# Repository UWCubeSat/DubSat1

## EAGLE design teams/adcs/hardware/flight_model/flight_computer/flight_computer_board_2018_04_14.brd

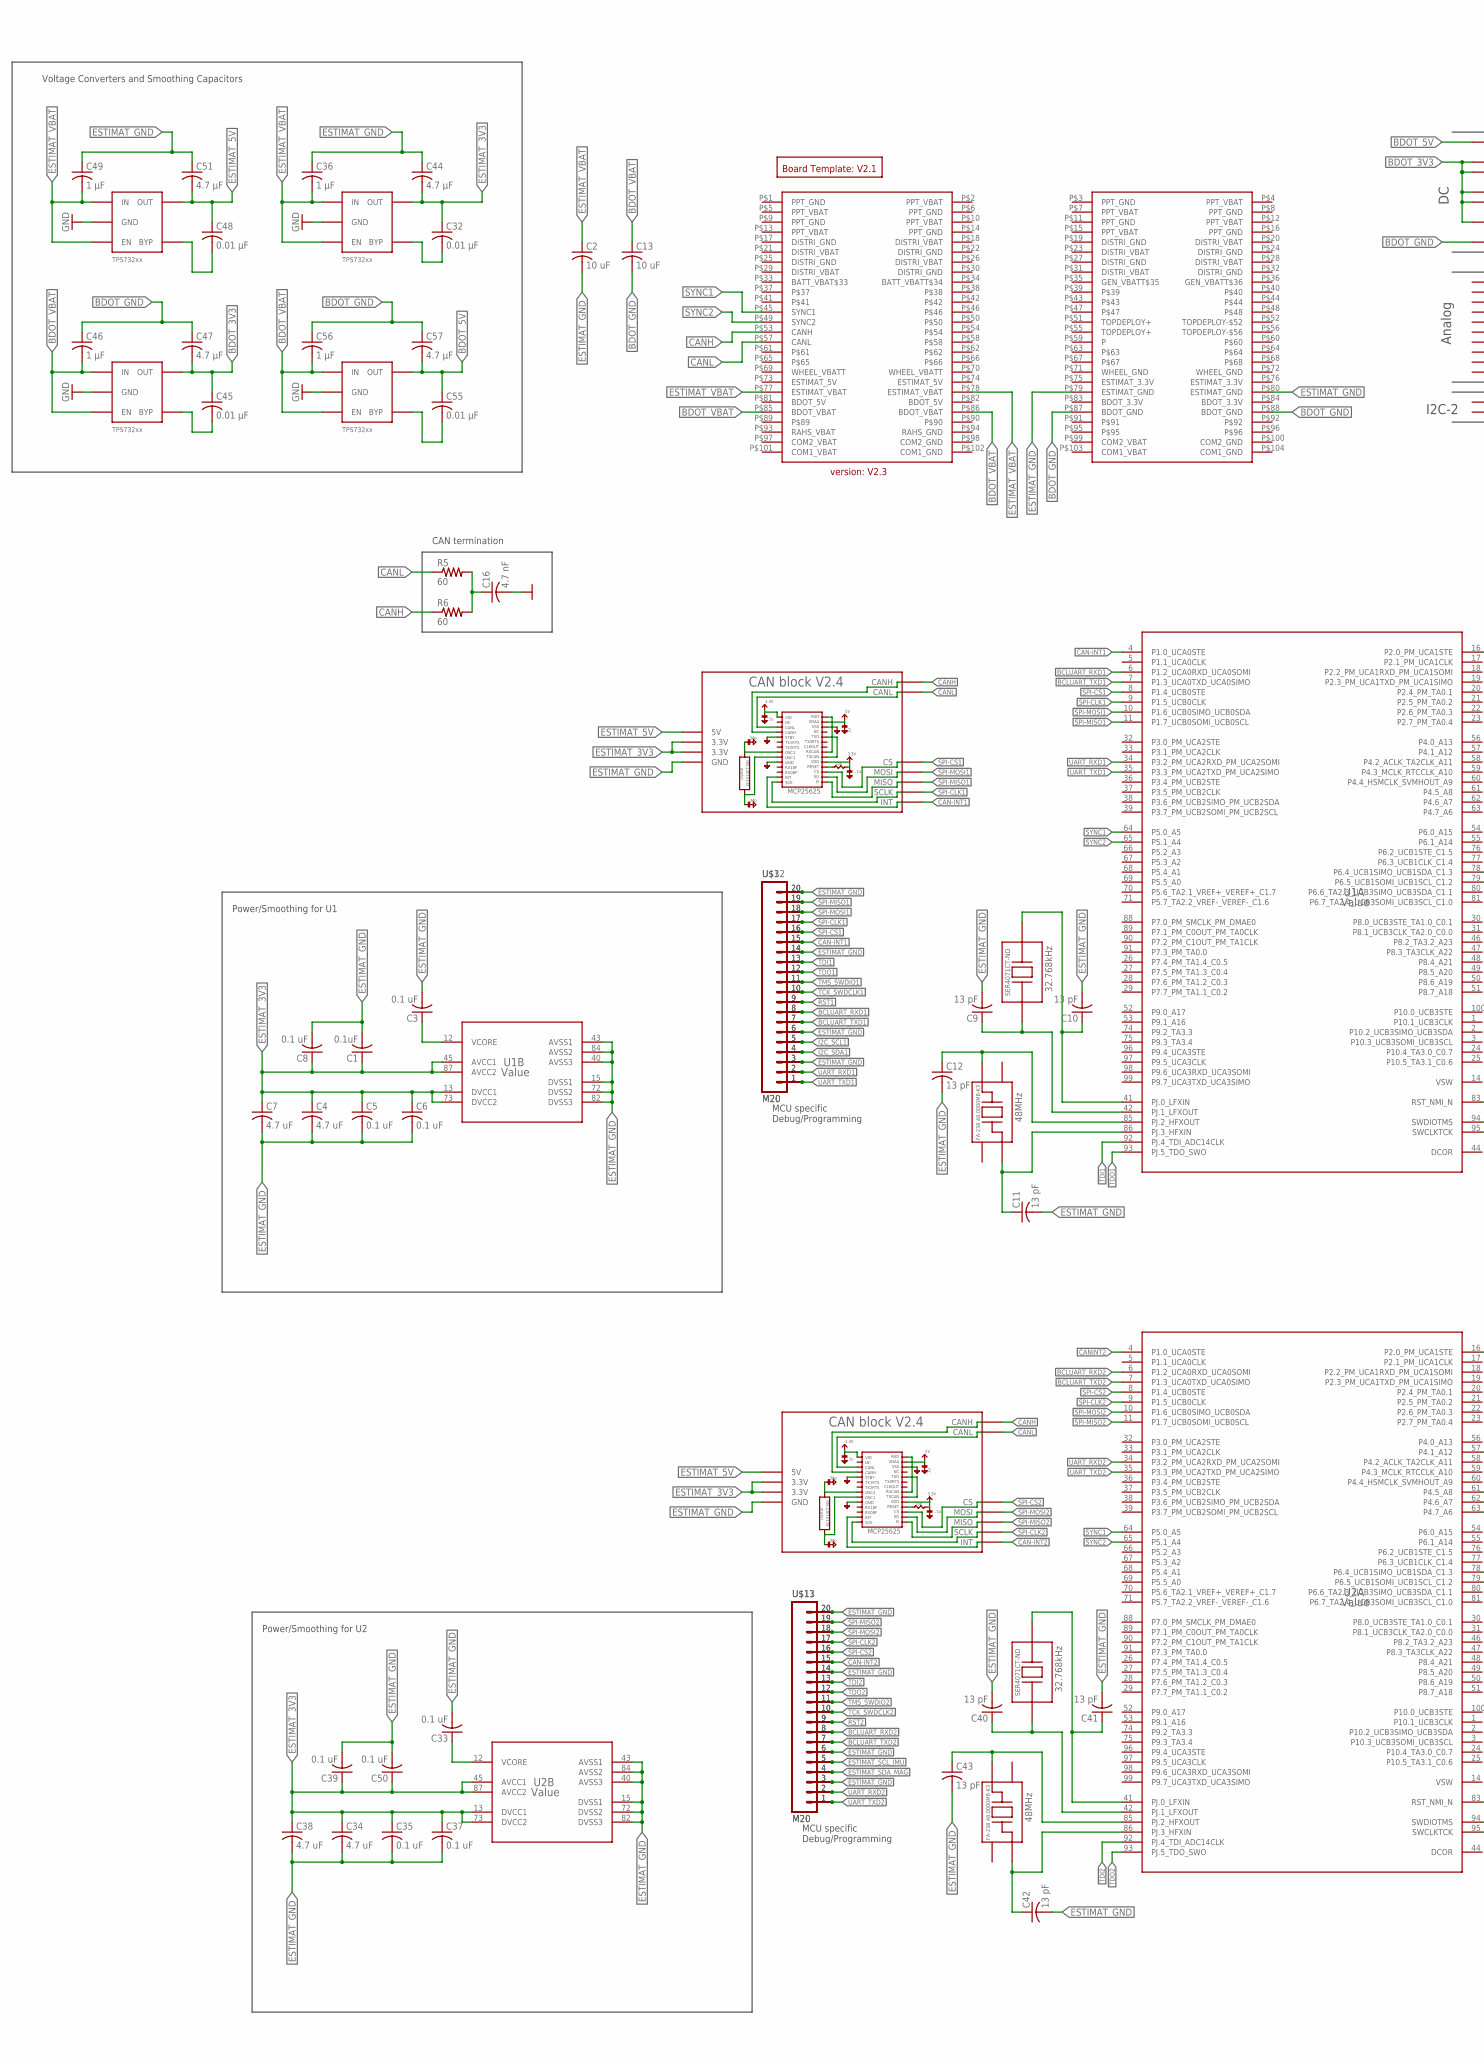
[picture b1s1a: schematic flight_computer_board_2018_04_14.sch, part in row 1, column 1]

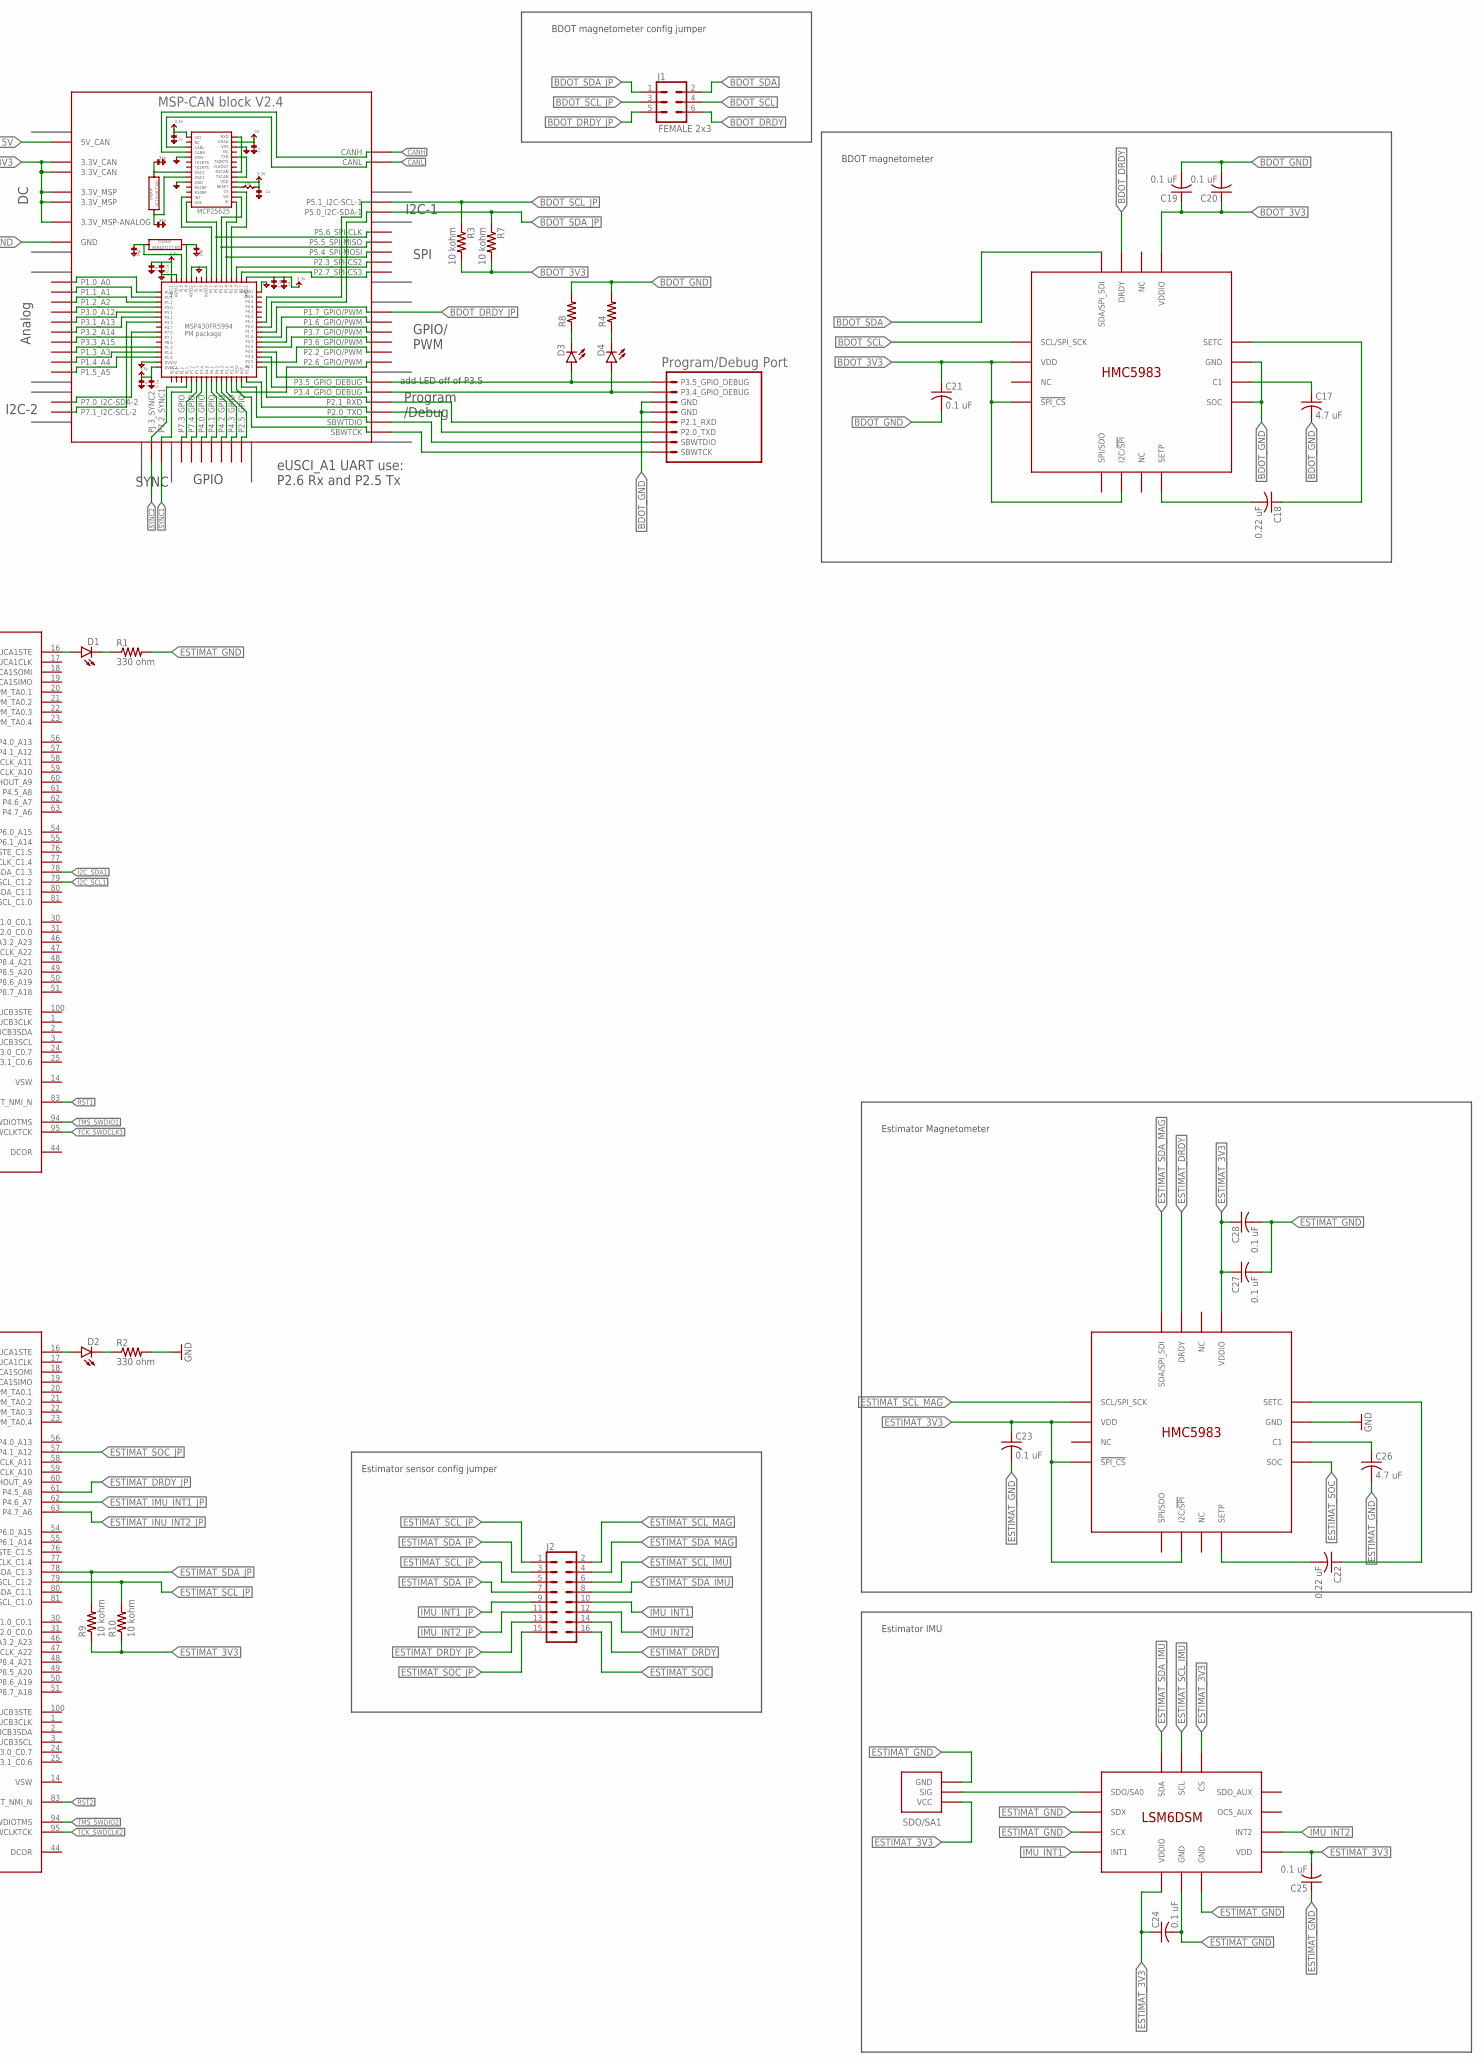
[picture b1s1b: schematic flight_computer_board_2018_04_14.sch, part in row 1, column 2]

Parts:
C1: 0.1uF; C0805
C2, C13: 10 uF; C0805
C3, C5, C6, C8, C19, C20, C21, C23, C24, C25, C27, C28, C33, C35, C37, C39, C50: 0.1 uF; C0805
C4, C7, C17, C26, C34, C38: 4.7 uF; C0805
C9, C10, C11, C12, C40, C41, C42, C43: 13 pF; C0805
C16: 4.7 nF; C0805
C18, C22: 0.22 uF; C0805
C32, C45, C48, C55: 0.01 μF; C0805
C36, C46, C49, C56: 1 μF; C0805
C44, C47, C51, C57: 4.7 μF; C0805
D1, D2, D3, D4: LED; LED-1206
J1: FEMALE 2x3; 2X3
J2: CONN_08X2; 2X8
R1, R2: 330 ohm; 0805
R3, R7, R9, R10: 10 kohm; 0805
R4, R8: RESISTOR0805; 0805
R5, R6: 60; 0805
SDO/SA1: 0_OHM_JUMPER
U1, U2: Value; PZ0100A_N
U4, U5, U6, U8: TPS732XX; SOT-23-5
U$1, U$4: EPSON_CRYSTAL_FC-135R; FC-135R
U$2, U$9: EPSON_CRYSTAL_FA-238; FA-238
U$3, U$11, U$12, U$13: M20; 1X20
U$5: BOARD_TEMPLATE1; BOARD_TEMPLATE
U$6: PC104_CONNECTOR
U$7: MSP-CAN_BLOCK
U$8, U$10: CAN_BLOCK
U$14: PROGRAM/DEBUG_PORT; 1X08_CONNECTOR
U$15, U$18: HMC5983
U$17: LSM6DSM

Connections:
BCLUART_RXD1: U1.6 (P1.2_UCA0RXD_UCA0SOMI), U$3.8, U$12.8
BCLUART_RXD2: U2.6 (P1.2_UCA0RXD_UCA0SOMI), U$11.8, U$13.8
BCLUART_TXD1: U1.7 (P1.3_UCA0TXD_UCA0SIMO), U$3.7, U$12.7
BCLUART_TXD2: U2.7 (P1.3_UCA0TXD_UCA0SIMO), U$11.7, U$13.7
BDOT_3V3: C19.1, C20.1, C21.1, C45.1, C47.2, R3.2, R7.2, U5.P$5 (OUT), U$7.3.3V@CAN1 (3.3V_CAN), U$7.3.3V@CAN2 (3.3V_CAN), U$7.3.3V@MSP1 (3.3V_MSP), U$7.3.3V@MSP2 (3.3V_MSP), U$7.3.3V_ANALOG@MSP2 (3.3V_MSP-ANALOG), U$15.!SPI_CS, U$15.I2C/!SPI, U$15.VDD, U$15.VDDIO
BDOT_5V: C55.1, C57.2, U8.P$5 (OUT), U$7.5V (5V_CAN)
BDOT_DRDY: J1.6, U$15.DRDY
BDOT_DRDY_JP: J1.5, U$7.P1.7_GPIO/PWM
BDOT_GND: C13.2, C17.2, C19.2, C20.2, C21.2, C46.1, C47.1, C56.1, C57.1, R4.2, R8.2, U5.P$2 (GND), U8.P$2 (GND), U$6.P$87 (BDOT_GND), U$6.P$88 (BDOT_GND), U$7.GND@1 (GND), U$7.GND@2 (GND), U$7.GND@3 (GND), U$7.GND@4 (GND), U$7.GND@5 (GND), U$7.GND@7 (GND), U$7.GND@8 (GND), U$7.GND@9 (GND), U$7.GND@10 (GND), U$7.GND@11 (GND), U$7.GND@12 (GND), U$7.GND@13 (GND), U$7.GND@14 (GND), U$7.GND@15 (GND), U$7.GND@16 (GND), U$7.GND@17 (GND), U$7.GND@26 (GND), U$14.5 (GND), U$14.6 (GND), U$15.GND, U$15.SOC
BDOT_LDO_3V3_BYP: C45.2, U5.P$4 (BYP)
BDOT_LDO_5V_BYP: C55.2, U8.P$4 (BYP)
BDOT_P3.4_GPIO_DEBUG: D4.A, U$7.P3.4_GPIO_DEBUG, U$14.7 (P3.4_GPIO_DEBUG)
BDOT_P3.5_GPIO_DEBUG: D3.A, U$7.P3.5_GPIO_DEBUG, U$14.8 (P3.5_GPIO_DEBUG)
BDOT_RXD: U$7.P2.1_RXD, U$14.4 (P2.1_RXD)
BDOT_SCL: J1.4, U$15.SCL/SPI_SCK
BDOT_SCL_JP: J1.3, R3.1, U$7.P5.1_I2C-SCL-1
BDOT_SDA: J1.2, U$15.SDA/SPI_SDI
BDOT_SDA_JP: J1.1, R7.1, U$7.P5.0_I2C-SDA-1
BDOT_TXD: U$7.P2.0_TXD, U$14.3 (P2.0_TXD)
BDOT_VBAT: C13.1, C46.2, C56.2, U5.P$1 (IN), U5.P$3 (EN), U8.P$1 (IN), U8.P$3 (EN), U$6.P$85 (BDOT_VBAT), U$6.P$86 (BDOT_VBAT)
CAN-INT1: U1.4 (P1.0_UCA0STE), U$3.15, U$8.INT, U$12.15
CAN-INT2: U$10.INT, U$11.15, U$13.15
CANH: R6.1, U$6.P$53 (CANH), U$7.CANH, U$8.CANH, U$10.CANH
CANINT2: U2.4 (P1.0_UCA0STE)
CANL: R5.1, U$6.P$57 (CANL), U$7.CANL, U$8.CANL, U$10.CANL
ESTIMAT_3V3: C1.1, C4.1, C5.1, C6.1, C7.1, C8.1, C23.1, C24.1, C25.2, C27.1, C28.1, C32.1, C34.1, C35.1, C37.1, C38.1, C39.1, C44.2, C50.1, R9.1, R10.1, SDO/SA1.P$3 (VCC), U1.13 (DVCC1), U1.45 (AVCC1), U1.73 (DVCC2), U1.87 (AVCC2), U2.13 (DVCC1), U2.45 (AVCC1), U2.73 (DVCC2), U2.87 (AVCC2), U4.P$5 (OUT), U$8.3.3V@CAN1 (3.3V), U$8.3.3V@CAN2 (3.3V), U$10.3.3V@CAN1 (3.3V), U$10.3.3V@CAN2 (3.3V), U$17.CS, U$17.VDD, U$17.VDDIO, U$18.!SPI_CS, U$18.I2C/!SPI, U$18.VDD, U$18.VDDIO
ESTIMAT_5V: C48.1, C51.2, U6.P$5 (OUT), U$8.5V, U$10.5V
ESTIMAT_DRDY: J2.14, U$18.DRDY
ESTIMAT_DRDY_JP: J2.13, U2.61 (P4.5_A8)
ESTIMAT_GND: C1.2, C2.2, C3.2, C4.2, C5.2, C6.2, C7.2, C8.2, C9.2, C10.2, C11.2, C12.2, C16.2, C23.2, C24.2, C25.1, C26.2, C27.2, C28.2, C33.2, C34.2, C35.2, C36.1, C37.2, C38.2, C39.2, C40.2, C41.2, C42.2, C43.2, C44.1, C49.1, C50.2, C51.1, R1.2, R2.2, SDO/SA1.P$1 (GND), U1.15 (DVSS1), U1.40 (AVSS3), U1.43 (AVSS1), U1.72 (DVSS2), U1.82 (DVSS3), U1.84 (AVSS2), U2.15 (DVSS1), U2.40 (AVSS3), U2.43 (AVSS1), U2.72 (DVSS2), U2.82 (DVSS3), U2.84 (AVSS2), U4.P$2 (GND), U6.P$2 (GND), U$3.3, U$3.6, U$3.14, U$3.20, U$6.P$79 (ESTIMAT_GND), U$6.P$80 (ESTIMAT_GND), U$8.GND@1 (GND), U$8.GND@2 (GND), U$8.GND@3 (GND), U$8.GND@4 (GND), U$8.GND@5 (GND), U$8.GND@11 (GND), U$8.GND@12 (GND), U$8.GND@13 (GND), U$10.GND@1 (GND), U$10.GND@2 (GND), U$10.GND@3 (GND), U$10.GND@4 (GND), U$10.GND@5 (GND), U$10.GND@11 (GND), U$10.GND@12 (GND), U$10.GND@13 (GND), U$11.3, U$11.6, U$11.14, U$11.20, U$12.3, U$12.6, U$12.14, U$12.20, U$13.3, U$13.6, U$13.14, U$13.20, U$17.GND@1 (GND), U$17.GND@2 (GND), U$17.SCX, U$17.SDX, U$18.GND
ESTIMAT_IMU_INT1_JP: U2.62 (P4.6_A7)
ESTIMAT_INU_INT2_JP: U2.63 (P4.7_A6)
ESTIMAT_LDO_3V3_BYP: C32.2, U4.P$4 (BYP)
ESTIMAT_LDO_5V_BYP: C48.2, U6.P$4 (BYP)
ESTIMAT_SCL_IMU: J2.6, U$11.5, U$13.5, U$17.SCL
ESTIMAT_SCL_JP: J2.1, J2.5, R10.2, U2.79 (P6.5_UCB1SOMI_UCB1SCL_C1.2)
ESTIMAT_SCL_MAG: J2.2, U$18.SCL/SPI_SCK
ESTIMAT_SDA_IMU: J2.8, U$17.SDA
ESTIMAT_SDA_JP: J2.3, J2.7, R9.2, U2.78 (P6.4_UCB1SIMO_UCB1SDA_C1.3)
ESTIMAT_SDA_MAG: J2.4, U$11.4, U$13.4, U$18.SDA/SPI_SDI
ESTIMAT_SOC: J2.16, U$18.SOC
ESTIMAT_SOC_JP: J2.15, U2.57 (P4.1_A12)
ESTIMAT_VBAT: C2.1, C36.2, C49.2, U4.P$1 (IN), U4.P$3 (EN), U6.P$1 (IN), U6.P$3 (EN), U$6.P$77 (ESTIMAT_VBAT), U$6.P$78 (ESTIMAT_VBAT)
I2C_SCL1: U1.79 (P6.5_UCB1SOMI_UCB1SCL_C1.2), U$3.5, U$12.5
I2C_SDA1: U1.78 (P6.4_UCB1SIMO_UCB1SDA_C1.3), U$3.4, U$12.4
IMU_INT1: J2.10, U$17.INT1
IMU_INT1_JP: J2.9
IMU_INT2: J2.12, U$17.INT2
IMU_INT2_JP: J2.11
unnamed: D2.A, U2.16 (P2.0_PM_UCA1STE)
unnamed: D2.C, R2.1
unnamed: D1.A, U1.16 (P2.0_PM_UCA1STE)
unnamed: D1.C, R1.1
unnamed: C3.1, U1.12 (VCORE)
unnamed: C10.1, U1.41 (PJ.0_LFXIN), U$1.P$2
unnamed: C9.1, U1.42 (PJ.1_LFXOUT), U$1.P$1
unnamed: C12.1, U1.85 (PJ.2_HFXOUT), U$2.P$3
unnamed: C11.1, U1.86 (PJ.3_HFXIN), U$2.P$1
unnamed: D4.C, R4.1
unnamed: C16.1, R5.2, R6.2
unnamed: D3.C, R8.1
unnamed: C17.1, U$15.C1
unnamed: C18.2, U$15.SETP
unnamed: C18.1, U$15.SETC
unnamed: SDO/SA1.P$2 (SIG), U$17.SDO/SA0
unnamed: C26.1, U$18.C1
unnamed: C22.2, U$18.SETP
unnamed: C22.1, U$18.SETC
unnamed: C40.1, U2.42 (PJ.1_LFXOUT), U$4.P$1
unnamed: C41.1, U2.41 (PJ.0_LFXIN), U$4.P$2
unnamed: C42.1, U2.86 (PJ.3_HFXIN), U$9.P$1
unnamed: C43.1, U2.85 (PJ.2_HFXOUT), U$9.P$3
RST1: U1.83 (RST_NMI_N), U$3.9, U$12.9
RST2: U2.83 (RST_NMI_N), U$11.9, U$13.9
SBWTCK: U$7.SBWTCK, U$14.SBWTCK
SBWTDIO: U$7.SBWTDIO, U$14.2 (SBWTDIO)
SPI-CLK1: U1.9 (P1.5_UCB0CLK), U$3.17, U$8.CLK (SCLK), U$12.17
SPI-CLK2: U2.9 (P1.5_UCB0CLK), U$10.CLK (SCLK), U$11.17, U$13.17
SPI-CS1: U1.8 (P1.4_UCB0STE), U$3.16, U$8.CS, U$12.16
SPI-CS2: U2.8 (P1.4_UCB0STE), U$10.CS, U$11.16, U$13.16
SPI-MISO1: U1.11 (P1.7_UCB0SOMI_UCB0SCL), U$3.19, U$8.MISO, U$12.19
SPI-MISO2: U2.11 (P1.7_UCB0SOMI_UCB0SCL), U$10.MISO, U$11.19, U$13.19
SPI-MOSI1: U1.10 (P1.6_UCB0SIMO_UCB0SDA), U$3.18, U$8.MOSI, U$12.18
SPI-MOSI2: U2.10 (P1.6_UCB0SIMO_UCB0SDA), U$10.MOSI, U$11.18, U$13.18
SYNC1: U1.64 (P5.0_A5), U2.64 (P5.0_A5), U$6.P$45 (SYNC1), U$7.P7.2_SYNC1
SYNC2: U1.65 (P5.1_A4), U2.65 (P5.1_A4), U$6.P$49 (SYNC2), U$7.PJ.3_SYNC2
TCK_SWDCLK1: U1.95 (SWCLKTCK), U$3.10, U$12.10
TCK_SWDCLK2: U2.95 (SWCLKTCK), U$11.10, U$13.10
TDI1: U1.92 (PJ.4_TDI_ADC14CLK), U$3.13, U$12.13
TDI2: U2.92 (PJ.4_TDI_ADC14CLK), U$11.13, U$13.13
TDO1: U1.93 (PJ.5_TDO_SWO), U$3.12, U$12.12
TDO2: U2.93 (PJ.5_TDO_SWO), U$11.12, U$13.12
TMS_SWDIO1: U1.94 (SWDIOTMS), U$3.11, U$12.11
TMS_SWDIO2: U2.94 (SWDIOTMS), U$11.11, U$13.11
UART_RXD1: U1.34 (P3.2_PM_UCA2RXD_PM_UCA2SOMI), U$3.2, U$12.2
UART_RXD2: U2.34 (P3.2_PM_UCA2RXD_PM_UCA2SOMI), U$11.2, U$13.2
UART_TXD1: U1.35 (P3.3_PM_UCA2TXD_PM_UCA2SIMO), U$3.1, U$12.1
UART_TXD2: U2.35 (P3.3_PM_UCA2TXD_PM_UCA2SIMO), U$11.1, U$13.1
VCORE: C33.1, U2.12 (VCORE)

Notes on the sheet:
MCU specific Debug/Programming
CAN termination
Voltage Converters and Smoothing Capacitors
Power/Smoothing for U2
Power/Smoothing for U1
Estimator IMU
Estimator Magnetometer
BDOT magnetometer
BDOT magnetometer config jumper
Estimator sensor config jumper

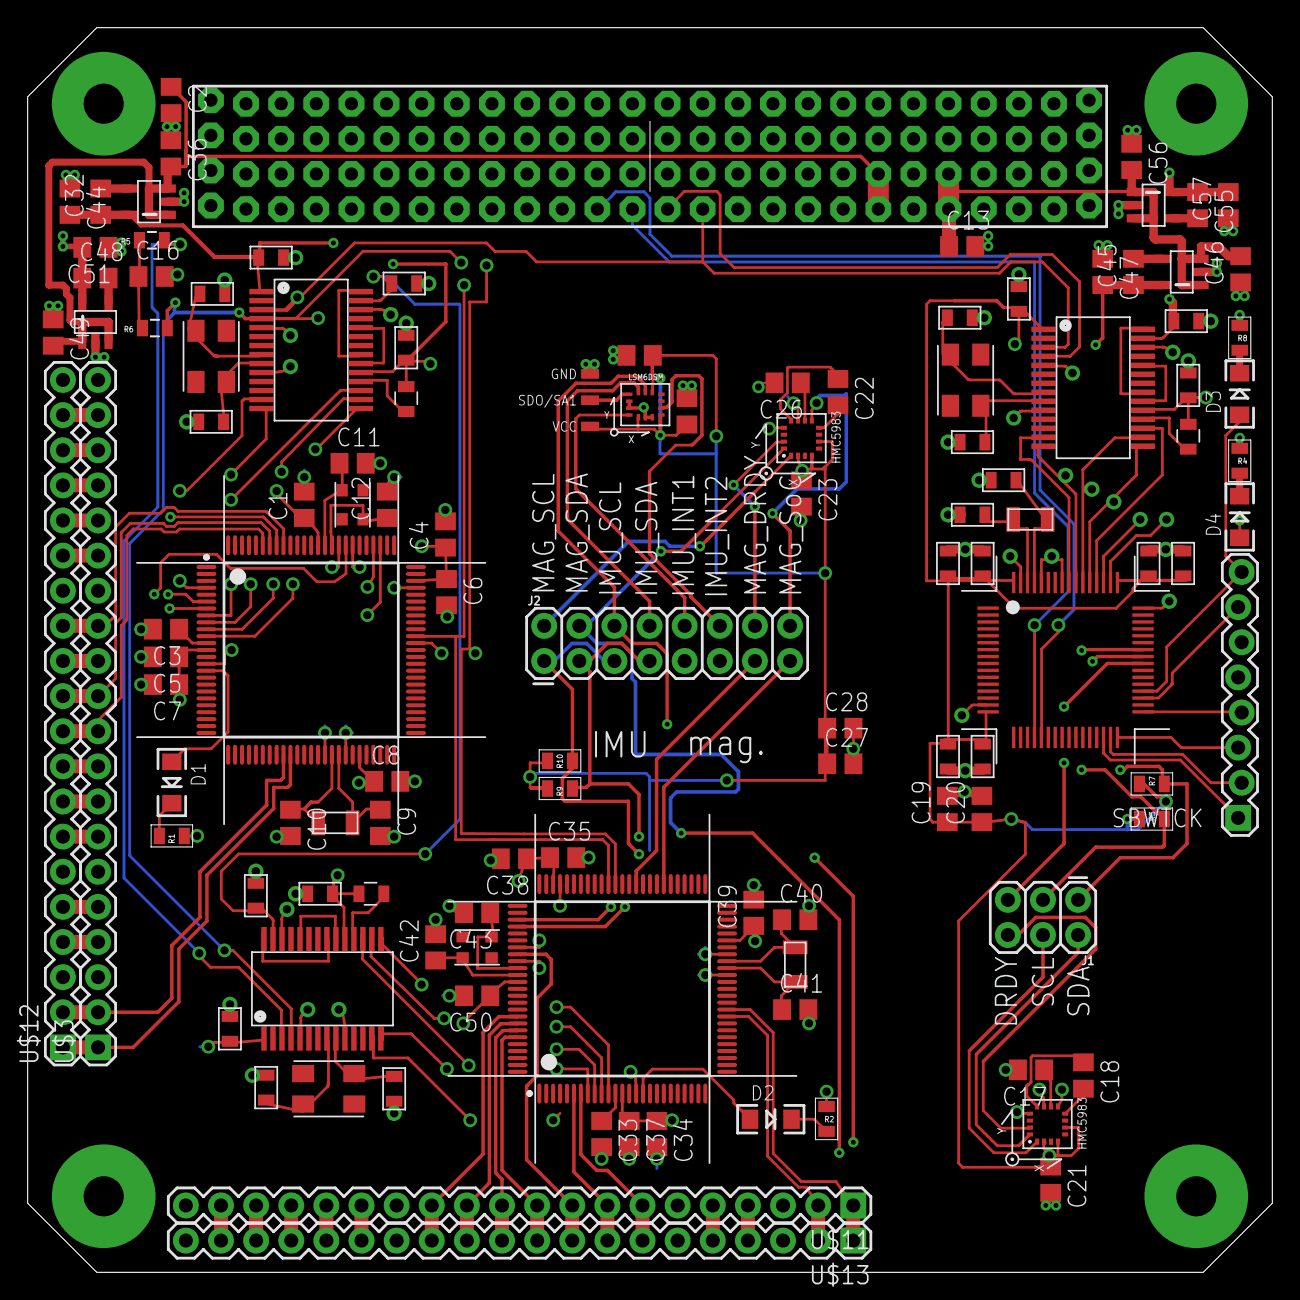
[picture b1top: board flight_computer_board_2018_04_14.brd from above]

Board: 4 copper layers, 90.0 x 90.0 mm, 89 parts (0 on the bottom side), 94 nets.

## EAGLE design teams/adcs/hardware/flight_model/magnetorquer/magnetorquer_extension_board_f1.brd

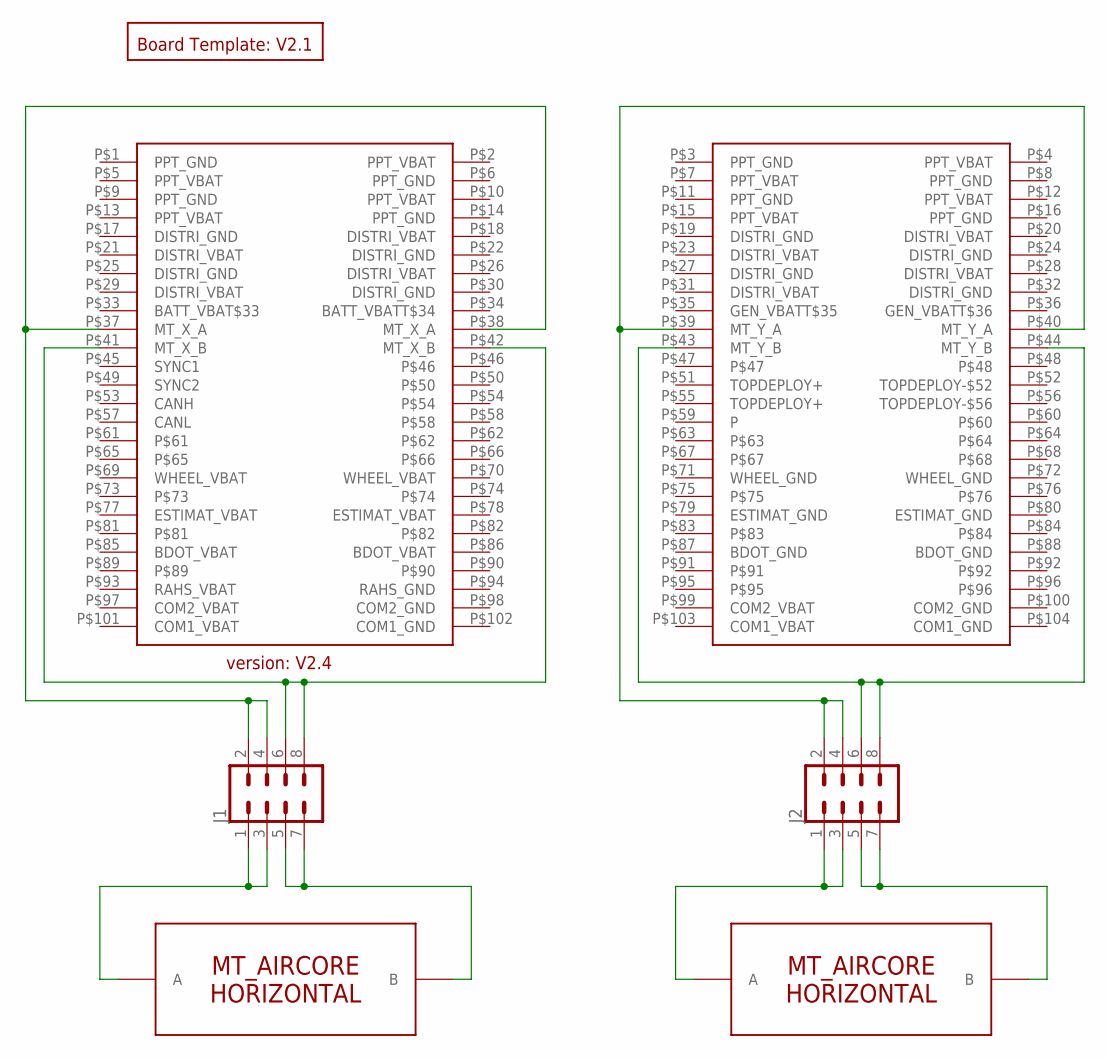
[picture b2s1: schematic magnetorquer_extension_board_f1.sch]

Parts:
J1, J2: CONN_04X2; 2X4
MT_X: MT_AIRCORE_HORIZONTAL
MT_Y: MT_AIRCORE_HORIZONTAL
U$1: PC104_CONNECTOR
U$2: BOARD_TEMPLATESERCURED; BOARD_TEMPLATE_SECURED

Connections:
MT_X_A: J1.1, J1.3, MT_X.A
MT_X_A_STACK: J1.2, J1.4, U$1.P$37 (MT_X_A), U$1.P$38 (MT_X_A)
MT_X_B: J1.5, J1.7, MT_X.B
MT_X_B_STACK: J1.6, J1.8, U$1.P$41 (MT_X_B), U$1.P$42 (MT_X_B)
MT_Y_A: J2.1, J2.3, MT_Y.A
MT_Y_A_STACK: J2.2, J2.4, U$1.P$39 (MT_Y_A), U$1.P$40 (MT_Y_A)
MT_Y_B: J2.5, J2.7, MT_Y.B
MT_Y_B_STACK: J2.6, J2.8, U$1.P$43 (MT_Y_B), U$1.P$44 (MT_Y_B)

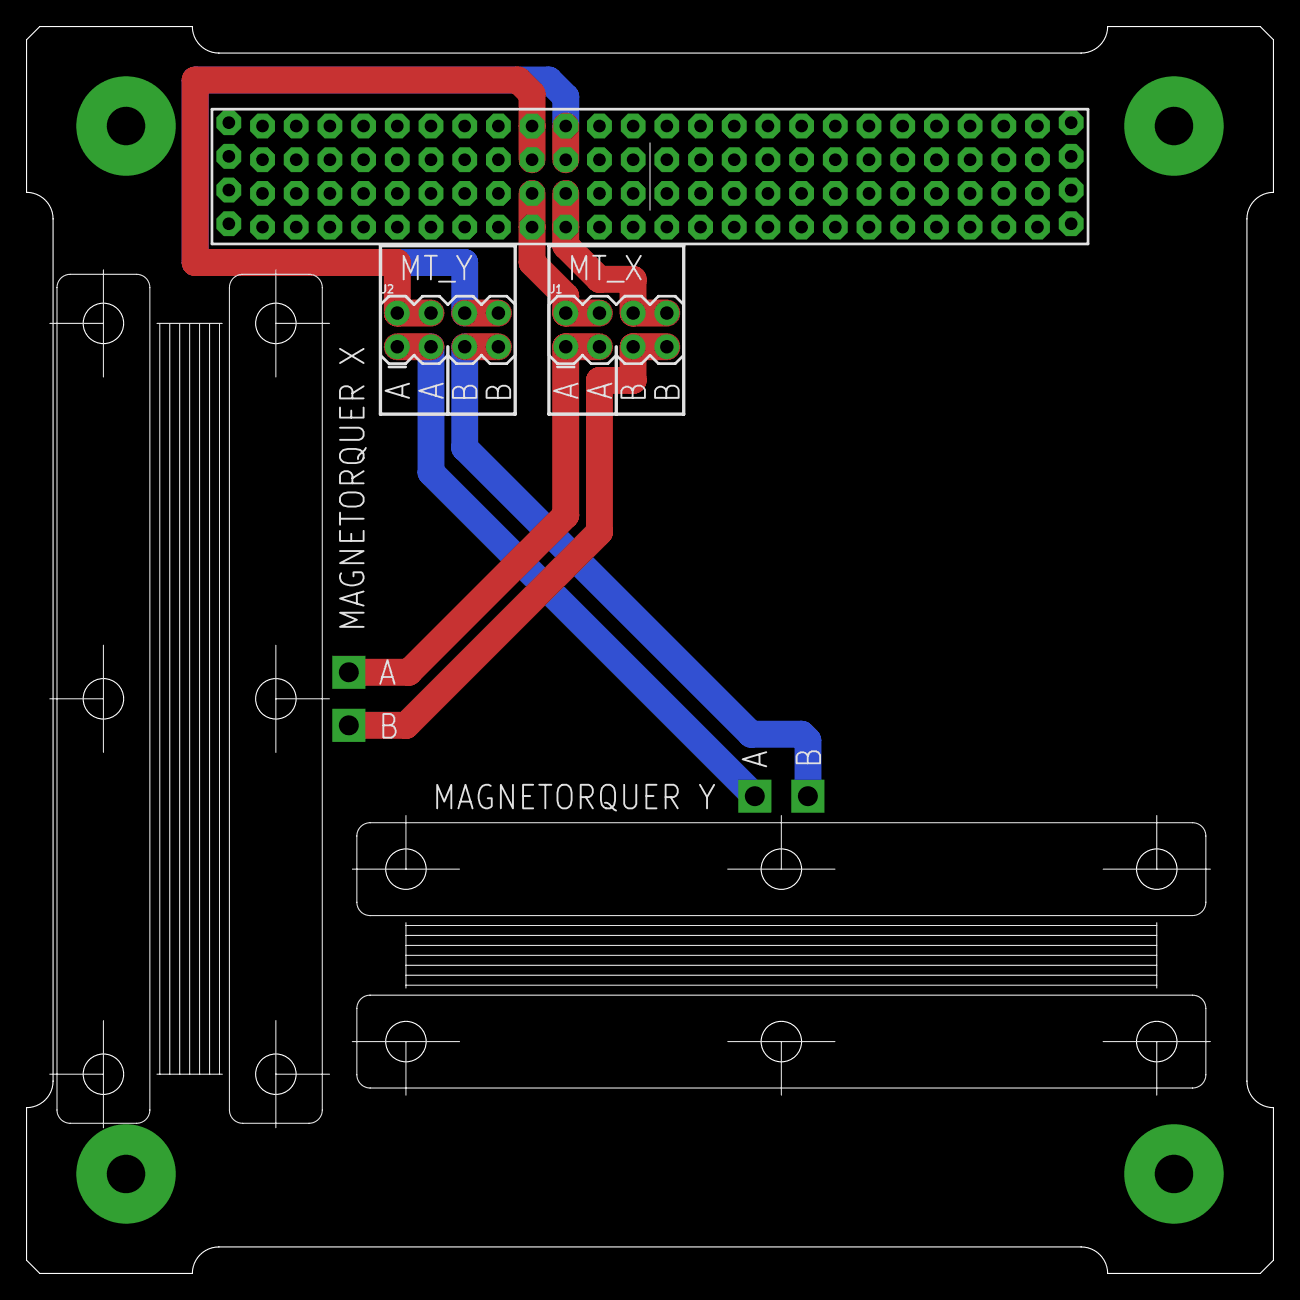
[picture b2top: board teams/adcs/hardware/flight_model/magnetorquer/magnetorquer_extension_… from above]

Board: 2 copper layers, 94.0 x 94.0 mm, 6 parts (0 on the bottom side), 8 nets.

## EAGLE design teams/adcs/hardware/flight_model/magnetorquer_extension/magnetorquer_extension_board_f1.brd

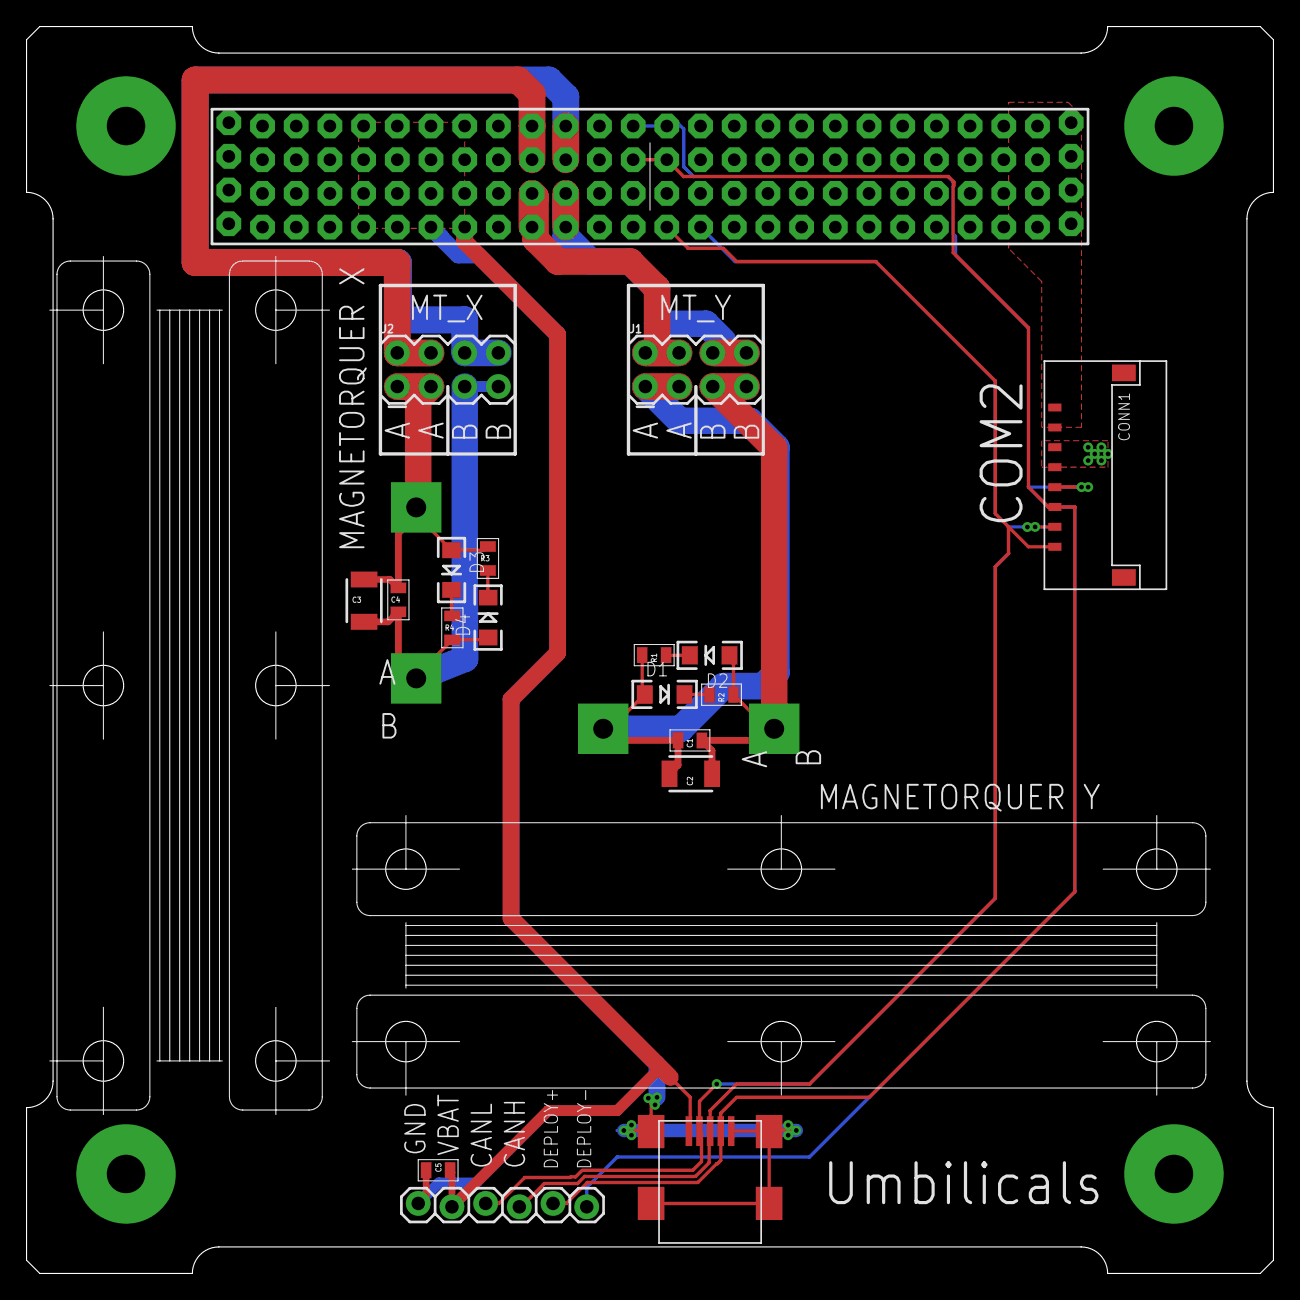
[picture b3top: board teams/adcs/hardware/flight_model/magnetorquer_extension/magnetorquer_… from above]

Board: 2 copper layers, 94.0 x 94.0 mm, 22 parts (0 on the bottom side), 20 nets.

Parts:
C1, C4: 0805
C2, C3: 1210
C5: .1u; 0805
CONN1: PICOLOCK_8PICOLOCK_8; PICOLOCK_8
D1, D2, D3, D4: LED-1206
J1, J2: 2X4
JP1: 1X06_LOCK
MT_X: MT_AIRCORE_HORIZONTAL
MT_Y: MT_AIRCORE_HORIZONTAL
R1, R2, R3, R4: 0805
U$1: PC104_CONNECTOR
U$2: BOARD_TEMPLATESERCURED; BOARD_TEMPLATE_SECURED
U$3: USB_MINI-B_AMPHENOL; USB_MINI_B

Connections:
CANH: CONN1.P$8, JP1.4, U$1.P$53, U$3.DATA+
CANL: CONN1.P$7, JP1.3, U$1.P$57, U$3.DATA-
COM2_GND: CONN1.P$3, CONN1.P$4, U$1.P$98, U$1.P$100
COM2_VBAT: CONN1.P$1, CONN1.P$2, U$1.P$97, U$1.P$99
GND: C5.2, JP1.1, U$1.P$17, U$1.P$19, U$1.P$22, U$1.P$24, U$1.P$25, U$1.P$27, U$1.P$30, U$1.P$32, U$3.GND1, U$3.GND2, U$3.GND3, U$3.GND4, U$3.GROUND
MT_X_A: C3.1, C4.1, D3.A, J2.1, J2.3, MT_Y.A, R3.1
MT_X_A_STACK: J2.2, J2.4, U$1.P$39, U$1.P$40
MT_X_B: C3.2, C4.2, D4.A, J2.5, J2.7, MT_Y.B, R4.2
MT_X_B_STACK: J2.6, J2.8, U$1.P$43, U$1.P$44
MT_Y_A: C1.1, C2.1, D1.A, J1.1, J1.3, MT_X.A, R1.1
MT_Y_A_STACK: J1.2, J1.4, U$1.P$37, U$1.P$38
MT_Y_B: C1.2, C2.2, D2.A, J1.5, J1.7, MT_X.B, R2.2
MT_Y_B_STACK: J1.6, J1.8, U$1.P$41, U$1.P$42
unnamed: D1.C, R2.1
unnamed: D2.C, R1.2
unnamed: D3.C, R4.1
unnamed: D4.C, R3.2
TOPDEPLOY+: CONN1.P$6, JP1.5, U$1.P$51, U$1.P$55, U$3.ID
TOPDEPLOY-: CONN1.P$5, JP1.6, U$1.P$52, U$1.P$56
VBAT: C5.1, JP1.2, U$1.P$18, U$1.P$20, U$1.P$21, U$1.P$23, U$1.P$26, U$1.P$28, U$1.P$29, U$3.VCC

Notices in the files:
parts and their libraries:
SparkFun-Connectors: Licensing: Creative Commons ShareAlike 4.0 International - https://creativecommons.org/licenses/by-sa/4.0
